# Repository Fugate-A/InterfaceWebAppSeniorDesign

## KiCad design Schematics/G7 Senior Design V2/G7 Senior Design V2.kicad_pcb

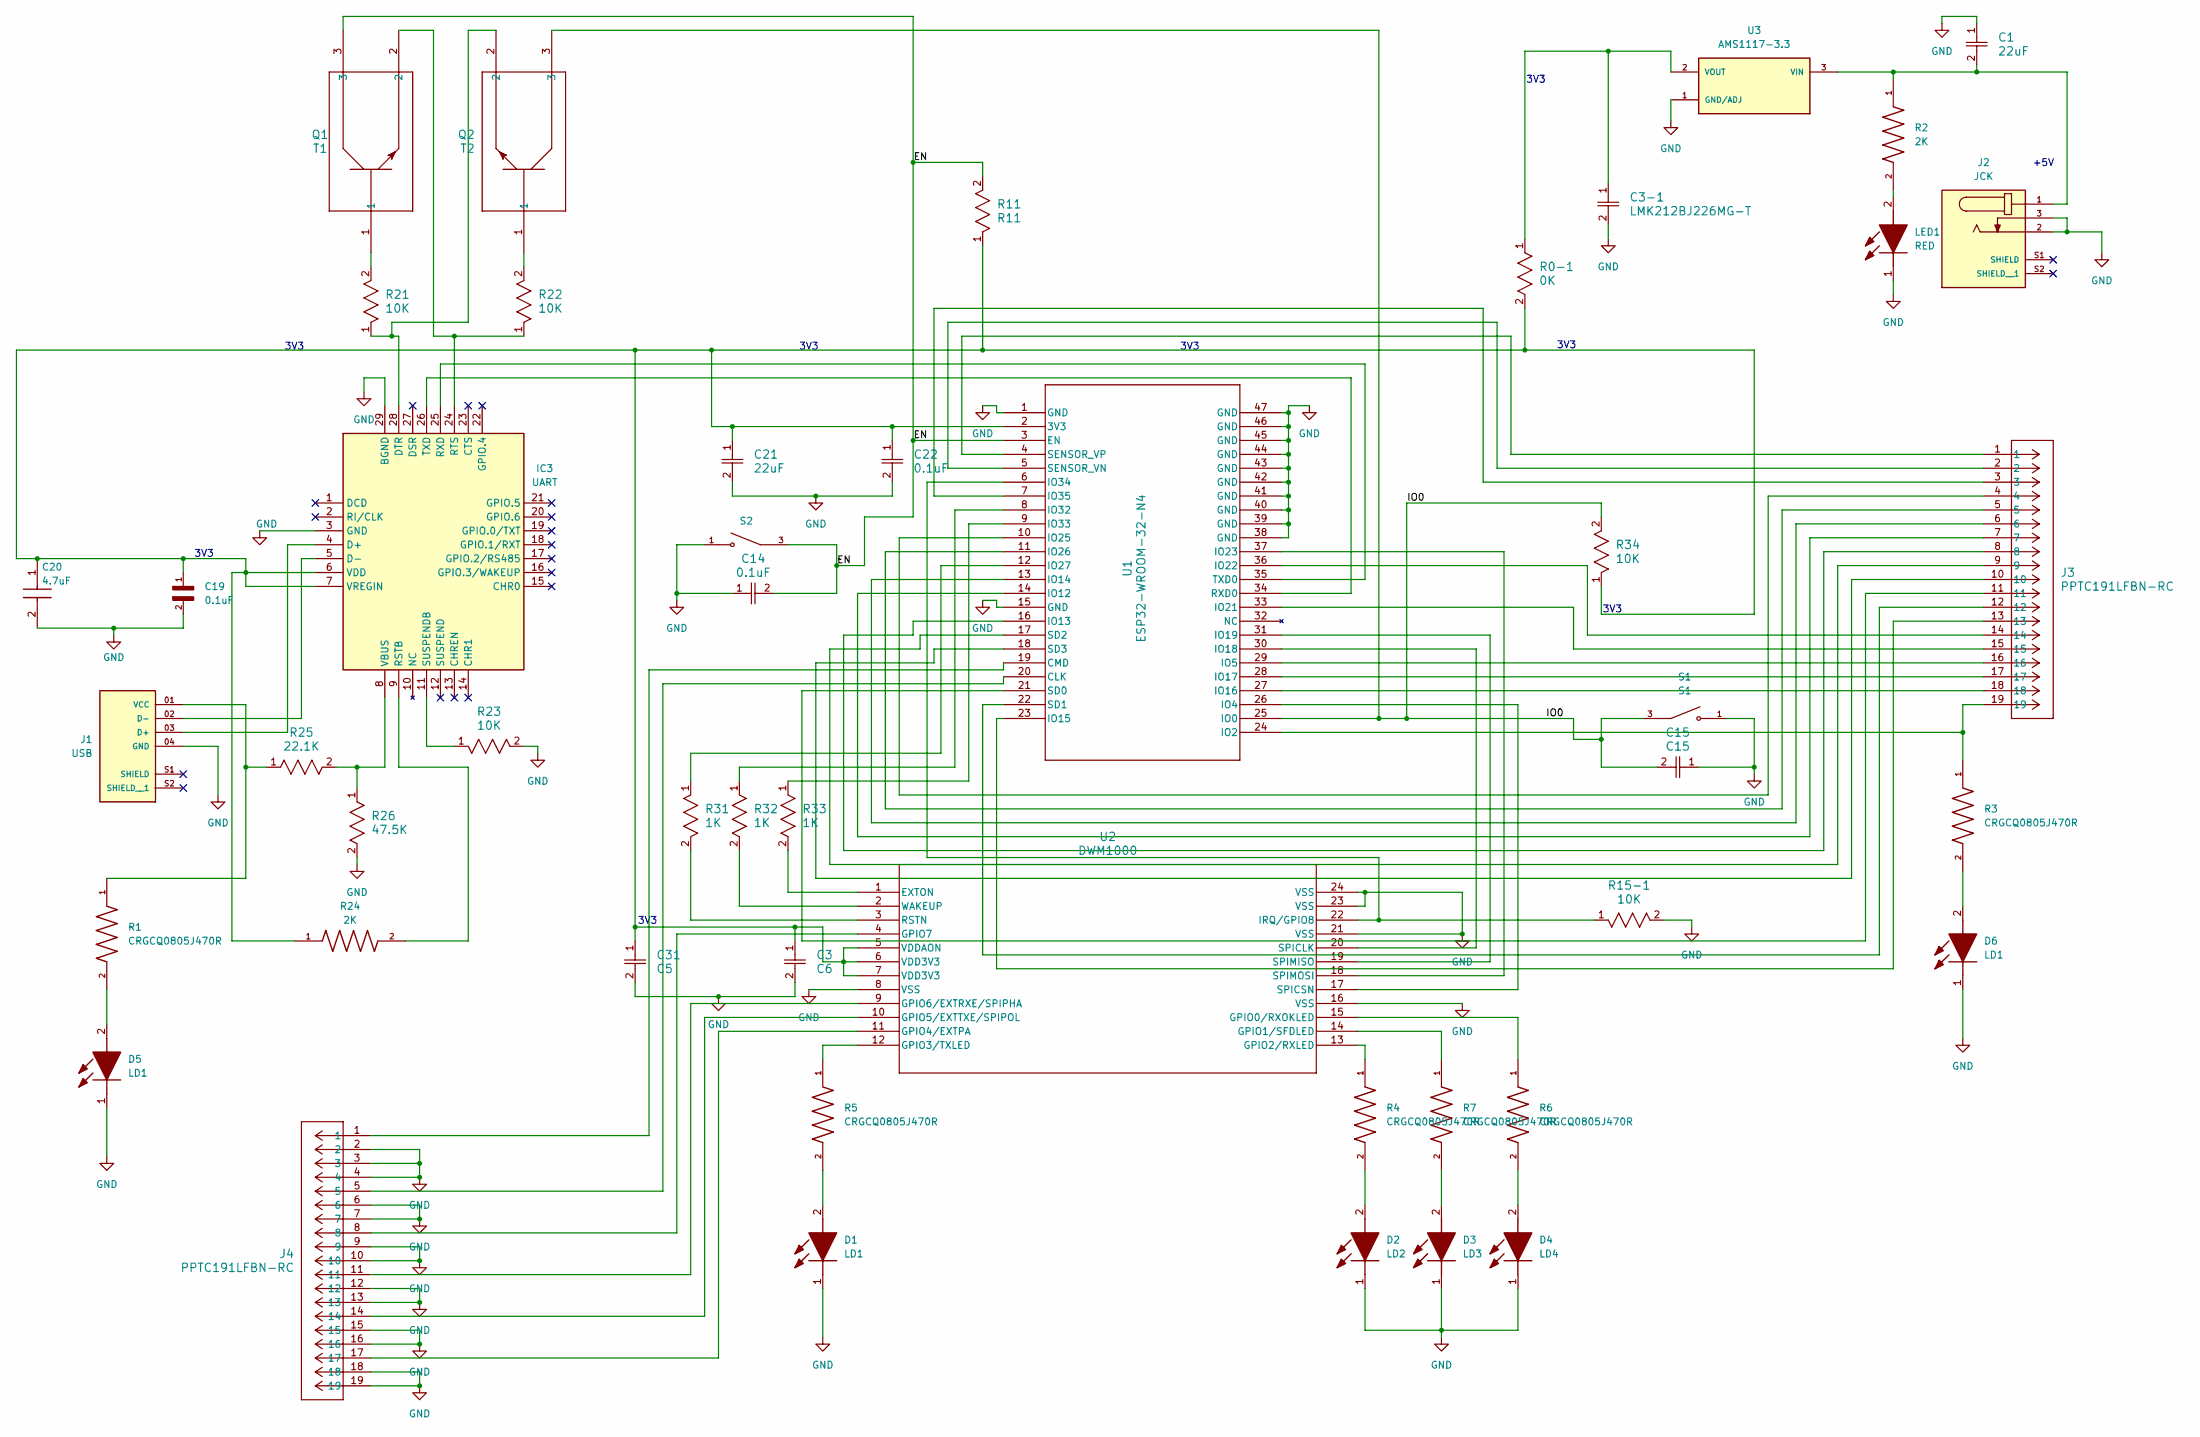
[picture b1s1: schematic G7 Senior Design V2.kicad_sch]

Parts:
C1, C21: 22uF; CAP_LMK212AB7106MG-T_TAY
C3: C6; CC0805N_YAG
C3-1: LMK212BJ226MG-T; CAP_LMK212AB7106MG-T_TAY
C14, C22: 0.1uF; CC0805N_YAG
C15: C15; CC0805N_YAG
C19: 0.1uF; CAPC2012X145N
C20: 4.7uF; CAPC2012X95N; Mouser Part Number 81-GRM219C80J475KE9D
C31: C5; CAP_LMK212AB7106MG-T_TAY
D1, D5, D6: LD1; LEDC2012X90N; Mouser Part Number 630-HSMW-C170-U0000
D2: LD2; LEDC2012X90N; Mouser Part Number 630-HSMW-C170-U0000
D3: LD3; LEDC2012X90N; Mouser Part Number 630-HSMW-C170-U0000
D4: LD4; LEDC2012X90N; Mouser Part Number 630-HSMW-C170-U0000
IC3: UART; QFN50P500X500X80-29N-D; Mouser Part Number 634-CP2102NA02GQFN28
J1: USB; AMPHENOL_87583-2010RLF; PARTREV AD
J2: JCK; CUI_PJ-051AH; PART_REV 1.0
J3, J4: PPTC191LFBN-RC; CONN19_PPTC191LFBN-RC_SUL
LED1: RED; LEDC2012X90N; Mouser Part Number 630-HSMW-C170-U0000
Q1: T1; TRAN_SS8050-G_CIP
Q2: T2; TRAN_SS8050-G_CIP
R0-1: 0K; STA_RMCF0805_STP
R1, R3, R4, R5, R6, R7: CRGCQ0805J470R; RESC2012X65N
R2, R24: 2K; RESC2012X60N
R11: R11; RC0805N_PAN
R15-1, R21, R22, R23, R34: 10K; RC0805N_PAN
R25: 22.1K; STA_RMCF0805_STP
R26: 47.5K; STA_RMCF080547.5K_STP
R31, R32, R33: 1K; RC0805N_YAG
S1: S1; SW_PTS_647_SN50_SMTR2_LFS; PARTREV 4 Apr 22
S2: S2; SW_PTS_647_SN50_SMTR2_LFS; PARTREV 4 Apr 22
U1: ESP32-WROOM-32-N4; MOD_ESP32-WROOM-32_EXP
U2: DWM1000; MOD_DWM1000_QOR
U3: AMS1117-3.3; SOT229P700X180-4N; PARTREV N/A

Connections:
/EN: C14.2, Q1.3, R11.2, S2.3, U1.3 (EN); also elsewhere on the board
/IO0: C15.2, Q2.3, R34.2, S1.3, U1.25 (IO0); also elsewhere on the board
GND: C1.1, C3.2, C3-1.2, C14.1, C15.1, C19.2, C20.2, C21.2, C22.2, C31.2, D1.1 (K), D2.1 (K), D3.1 (K), D4.1 (K), D5.1 (K), D6.1 (K), IC3.3 (GND), IC3.29 (BGND), J1.04 (GND), J2.2, J2.3, J4.2, J4.3, J4.4, J4.6, J4.7, J4.9, J4.10, J4.12, J4.13, J4.15, J4.16, J4.18, J4.19, LED1.1 (K), R15-1.2, R23.2, R26.2, S1.1, S2.1, U1.1 (GND), U1.15 (GND), U1.38 (GND), U1.39 (GND), U1.40 (GND), U1.41 (GND), U1.42 (GND), U1.43 (GND), U1.44 (GND), U1.45 (GND), U1.46 (GND), U1.47 (GND), U2.8 (VSS), U2.16 (VSS), U2.21 (VSS), U2.23 (VSS), U2.24 (VSS), U3.1 (GND/ADJ); also elsewhere on the board
unnamed: D1.2 (A), R5.2
unnamed: D2.2 (A), R4.2
unnamed: D3.2 (A), R7.2
unnamed: D4.2 (A), R6.2
unnamed: D5.2 (A), R1.2
unnamed: D6.2 (A), R3.2
unnamed: IC3.4 (D+), J1.03 (D+)
unnamed: IC3.5 (D-), J1.02 (D-)
unnamed: IC3.28 (DTR), Q2.2, R21.1
unnamed: IC3.9 (RSTB), R24.2
unnamed: IC3.24 (RTS), Q1.2, R22.1
unnamed: IC3.25 (RXD), U1.35 (TXD0)
unnamed: IC3.11 (SUSPENDB), R23.1
unnamed: IC3.26 (TXD), U1.34 (RXD0)
unnamed: IC3.8 (VBUS), R25.2, R26.1
unnamed: C3.1, C19.1, C20.1, C21.1, C22.1, C31.1, IC3.6 (VDD), IC3.7 (VREGIN), R0-1.2, R11.1, R24.1, R34.1, U1.2 (3V3), U2.5 (VDDAON), U2.6 (VDD3V3), U2.7 (VDD3V3)
unnamed: J1.01 (VCC), R1.1, R25.1
unnamed: LED1.2 (A), R2.2
unnamed: Q1.1, R21.2
unnamed: Q2.1, R22.2
unnamed: J4.5, U1.20 (CLK)
unnamed: J4.1, U1.19 (CMD)
unnamed: J3.19, R3.1, U1.24 (IO2)
unnamed: U1.26 (IO4), U2.17 (SPICSN)
unnamed: J3.16, U1.29 (IO5)
unnamed: J3.7, U1.14 (IO12)
unnamed: J3.8, U1.16 (IO13)
unnamed: J3.6, U1.13 (IO14)
unnamed: J3.13, U1.23 (IO15)
unnamed: J3.18, U1.27 (IO16)
unnamed: J3.17, U1.28 (IO17)
unnamed: U1.30 (IO18), U2.20 (SPICLK)
unnamed: U1.31 (IO19), U2.19 (SPIMISO)
unnamed: J3.15, U1.33 (IO21)
unnamed: J3.14, U1.36 (IO22)
unnamed: U1.37 (IO23), U2.18 (SPIMOSI)
unnamed: J3.4, U1.10 (IO25)
unnamed: J3.5, U1.11 (IO26)
unnamed: R31.1, U1.12 (IO27)
unnamed: R32.1, U1.8 (IO32)
unnamed: R33.1, U1.9 (IO33)
unnamed: R15-1.1, U1.6 (IO34), U2.22 (IRQ/GPIO8)
unnamed: J3.3, U1.7 (IO35)
unnamed: J3.11, U1.21 (SD0)
unnamed: J3.12, U1.22 (SD1)
unnamed: J3.9, U1.17 (SD2)
unnamed: J3.10, U1.18 (SD3)
unnamed: J3.2, U1.5 (SENSOR_VN)
unnamed: J3.1, U1.4 (SENSOR_VP)
unnamed: R33.2, U2.1 (EXTON)
unnamed: R6.1, U2.15 (GPIO0/RXOKLED)
unnamed: R7.1, U2.14 (GPIO1/SFDLED)
unnamed: R4.1, U2.13 (GPIO2/RXLED)
unnamed: R5.1, U2.12 (GPIO3/TXLED)
unnamed: J4.17, U2.11 (GPIO4/EXTPA)
unnamed: J4.14, U2.10 (GPIO5/EXTTXE/SPIPOL)
unnamed: J4.11, U2.9 (GPIO6/EXTRXE/SPIPHA)
unnamed: J4.8, U2.4 (GPIO7)
unnamed: R31.2, U2.3 (RSTN)
unnamed: R32.2, U2.2 (WAKEUP)
unnamed: C1.2, J2.1, R2.1, U3.3 (VIN)
unnamed: C3-1.1, R0-1.1, U3.2 (VOUT)

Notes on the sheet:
3V3
+5V

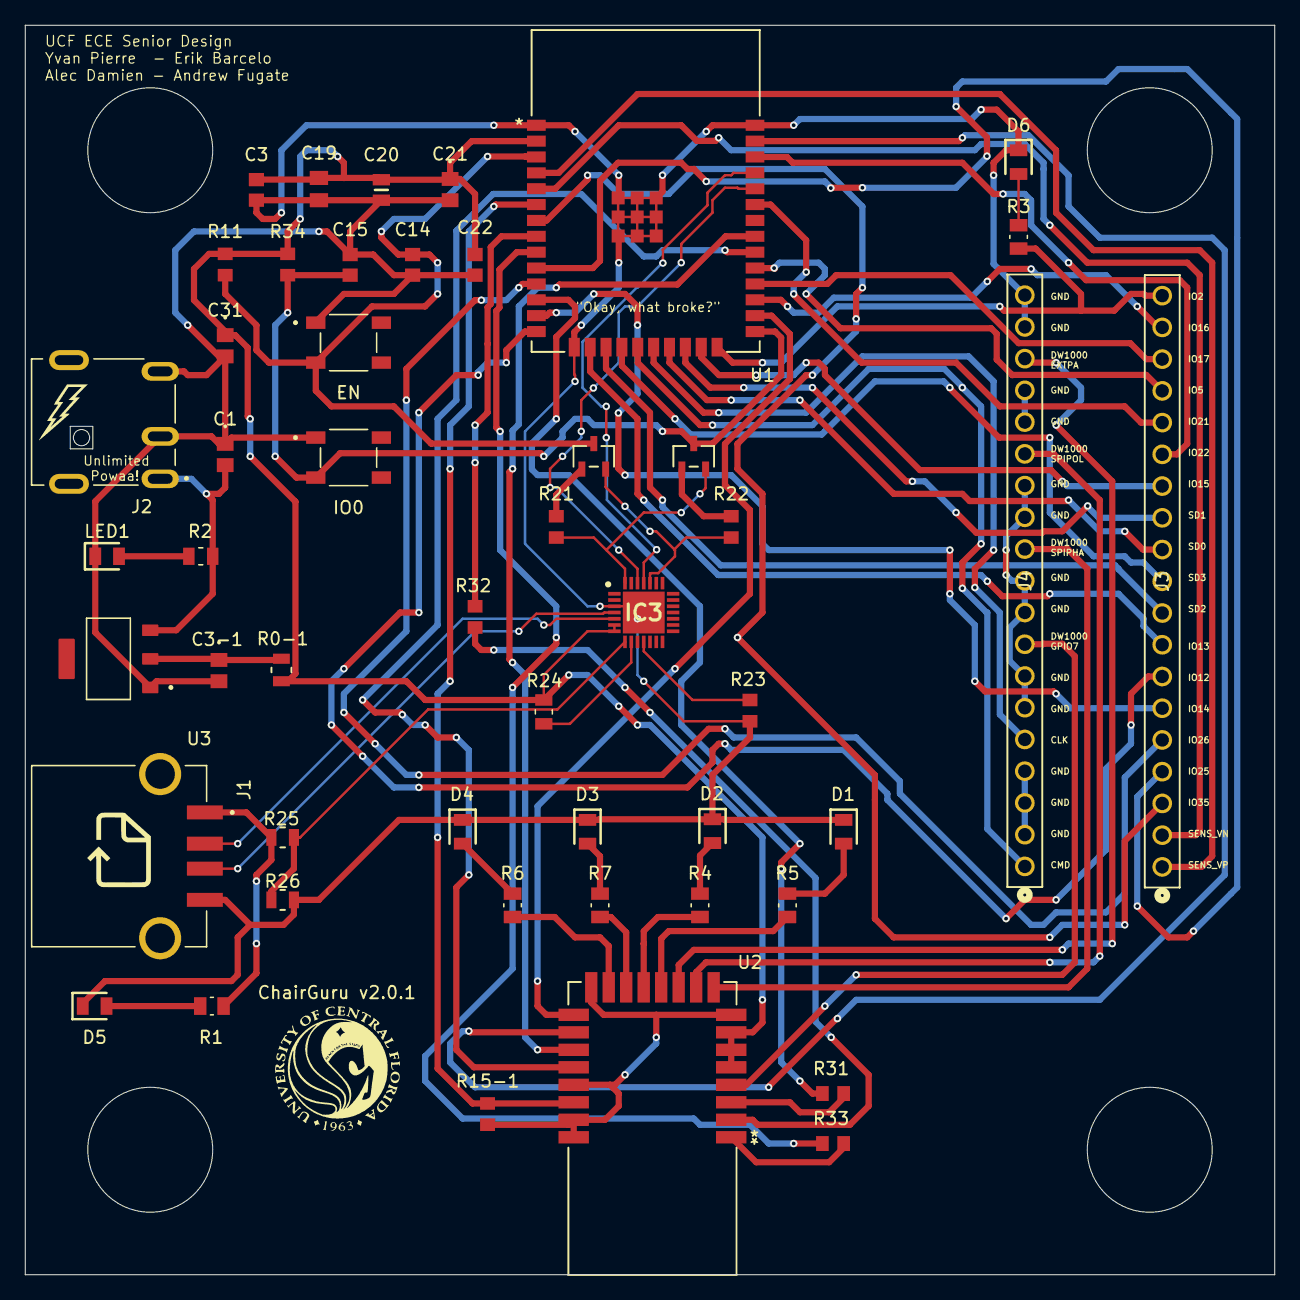
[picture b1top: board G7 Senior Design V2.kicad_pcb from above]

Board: 2 copper layers, 100.0 x 100.0 mm, 49 parts (0 on the bottom side), 65 nets.

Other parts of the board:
EN: S2; SW_PTS_647_SN50_SMTR2_LFS
IO0: S1; SW_PTS_647_SN50_SMTR2_LFS

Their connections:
/EN: EN.3; also elsewhere on the board
/IO0: IO0.3; also elsewhere on the board
GND: EN.1, IO0.1; also elsewhere on the board

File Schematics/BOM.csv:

"Id;""Designator"";""Footprint"";""Quantity"";""Designation"";""Supplier and ref"";",,,,
"1;""J4","J3"";""CONN19_PPTC191LFBN-RC_SUL"";2;""PPTC191LFBN-RC"";;;",,,
"2;""C1","C21"";""CAP_LMK212AB7106MG-T_TAY"";2;""22uF"";;;",,,
"3;""R26"";""STA_RMCF080547.5K_STP"";1;""47.5K"";;;",,,,
"4;""D2"";""LEDC2012X90N"";1;""LD2"";;;",,,,
"5;""S2"";""SW_PTS_647_SN50_SMTR2_LFS"";1;""S2"";;;",,,,
"6;""R11"";""RC0805N_PAN"";1;""R11"";;;",,,,
"7;""R25"";""STA_RMCF0805_STP"";1;""22.1K"";;;",,,,
"8;""D1"";""LEDC2012X90N"";1;""LD1"";;;",,,,
"9;""C14","C22"";""CC0805N_YAG"";2;""0.1uF"";;;",,,
"10;""R6",R5,R4,"R7"";""RESC2012X65N"";4;""CRGCQ0805J470R"";;;",
"11;""J2"";""CUI_PJ-051AH"";1;""JCK"";;;",,,,
"12;""U2"";""MOD_DWM1000_QOR"";1;""DWM1000"";;;",,,,
"13;""C19"";""CAPC2012X95N"";1;""0.1uF"";;;",,,,
"14;""R32"";""RES_1220_SUS"";1;""RD2"";;;",,,,
"15;""C31"";""CAP_LMK212AB7106MG-T_TAY"";1;""C5"";;;",,,,
"16;""J1"";""AMPHENOL_87583-2010RLF"";1;""USB"";;;",,,,
"17;""R2","R24"";""RESC2012X60N"";2;""2K"";;;",,,
"18;""R22",R15-1,R23,R21,"R34"";""RC0805N_PAN"";5;""10K"";;;"
"19;""D3"";""LEDC2012X90N"";1;""LD3"";;;",,,,
"20;""Q1"";""TRAN_SS8050-G_CIP"";1;""T1"";;;",,,,
"21;""C3"";""CC0805N_YAG"";1;""C6"";;;",,,,
"22;""R33"";""RES_1220_SUS"";1;""RD3"";;;",,,,
"23;""C15"";""CC0805N_YAG"";1;""C15"";;;",,,,
"24;""C20"";""CAPC2012X95N"";1;""4.7uF"";;;",,,,
"25;""S1"";""SW_PTS_647_SN50_SMTR2_LFS"";1;""S1"";;;",,,,
"26;""U1"";""MOD_ESP32-WROOM-32_EXP"";1;""ESP32-WROOM-32-N4"";;;",,,,
"27;""D4"";""LEDC2012X90N"";1;""LD4"";;;",,,,
"28;""U3"";""SOT229P700X180-4N"";1;""AMS1117-3.3"";;;",,,,
"29;""LED1"";""LEDC2012X90N"";1;""RED"";;;",,,,
"30;""Q2"";""TRAN_SS8050-G_CIP"";1;""T2"";;;",,,,
"31;""IC3"";""QFN50P500X500X80-29N-D"";1;""UART"";;;",,,,
"32;""R0-1"";""STA_RMCF0805_STP"";1;""0K"";;;",,,,
"33;""C3-22uF1"";""CAP_LMK212AB7106MG-T_TAY"";1;""LMK212BJ226MG-T"";;;",,,,
"34;""R31"";""RES_1220_SUS"";1;""RD1"";;;",,,,

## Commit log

2024-07-10 Init react proj
2024-07-10 Setup Phase
    frontend and backend working with cors setup and interaction tested at a basic level, web app ready to be developed
2024-07-10 most filler react code axed and no errors
2024-07-25 ignoring personal workspace file
2024-07-25 small updates for routing
2024-07-26 routes working, new page, lrud movement added, working on rotation
2024-07-28 ROTATION AND MOVEMENT working !!!
2024-07-28 Colliosion blocking added
2024-07-30 getting ready for more interconnectivity via env and server js
2024-08-19 .env added to ignore
2024-08-22 api for saving works via postman, working for port 5000 but react stuck on 3000, need to add load feature after fixing this
2024-08-22 saving to mongo atlas works!!! now need to load from mongo
2024-08-23 reading id from mongo works now need to rework to display the reads and not just id
2024-08-23 api.js comments cleaned up for da ocd
2024-09-03 updated index, api, and server .js files preparing for merge and collaberators. Fixed mongo names to be real rather than the testing/implementing phase
2024-09-03 FavIcon and tab name updated as well as some of App.js
2024-09-03 create layout page works with adding of custom box layouts, merging before contuning to load
2024-09-04 loading configs to visaulize works but needs adjusting, nothing breaking rn, needs to make new branch cuz i forgor
2024-09-05 Layout list page displays name of layout saved in mongo
2024-09-06 stashing changes - not working
2024-09-06 adding folder for eric to add schematic of PCB
2024-09-06 not working but committing before losing lol
2024-09-06 adding text box
    just to learn Git, we put a text box!!!!!!!!!!!!!!
2024-09-09 Added Changes from Last Meeting
2024-09-09 random kicad stuff
2024-09-09 Weeks Revision before Jungle of Words
2024-09-09 labels adjusted
2024-09-12 First Version to be Ordered from JLCPCB
    Associated schematic with first Gerber file to be sent out to JLCPCB to be fabricated.
2024-09-12 Ensuring Git-Push prior to ordering
2024-09-12 added logos and final review, going to order
2024-09-12 One Page Error Report Gerber
2024-09-12 Initial BOM added
2024-09-13 Updated Gerber and BOM 13 SEP 24
2024-10-01 overview now shoes 1 config, need to update display but works for that
2024-10-03 commit arduino stuff forgetting schematic changes
2024-10-03 testing stuff
    dw1000 communciates but code doesnt work, still a dub
2024-10-06 ChairGuru V1.1
    Updated Changes According to Doc as of 06 OCT 24.
2024-10-07 current in lab model
2024-10-07 ChairGuru 7 OCT 24 NIGHT
    Andrew's Updated Content
2024-10-11 ChairGuru V2.0.1
    11 OCT 24 Updates
2024-10-11 added esp data sheet
2024-10-12 Overview shows chairs now yay
2024-10-12 path planning but no reotation remberance, intial implementation without refinment, generic algo's
2024-10-12 handles x and y movement and then finishes with rotation, good stopping point until antenna integration is needed
2024-10-16 DRV8825 V1
    Custom PCB for Motor Drivers
2024-10-17 css stuff added and env updated to allow for ip access from hotspot
2024-10-17 collision avoidance early imp.. done for night
2024-10-21 init motor code branch
2024-10-21 esp connects to wifi and loops to continue checking status
2024-10-21 updated package json details and working on websocket
    websocket connects but now adding manual testing and then autoamted sending
2024-10-22 not working comms
    esp connects to wifi but does not maintain websocket connection, incoudes esp code and socket.js code
2024-10-23 Added 4 motor code to drive forward
2024-10-23 motor code for 4 motors on v2.0.1 board headers
2024-10-23 space
2024-10-23 working pin out and directory for 4 motor control
2024-10-24 testing library for soft-AP use case
2024-10-24 esp soft-ap working and logging simple http button request from x device to esp32 console
2024-10-24 Websocket is working and full-duplex between a third party device and esp communicate to server pc
2024-10-31 triangle push, may delete later
2024-11-01 Triangulation Code update
    Update, all functional, missing 2nd tag code. Distance calculation afterward
2024-11-01 Test on Chassis
2024-11-04 Updated Motor Code. Everything is accurate except rotation.
2024-11-04 Bug fixes
2024-11-05 not working with motor code but esp hotspot is somwhat working, added api call on overview.js
2024-11-05 wireless netwroking from server now controls motors via access point
2024-11-06 updated motor code and addded buttons to frontend for testing
2024-11-08 Update of Triangulation-Code
    Anchor Code1/2 - Officially ready and done.
    Tag Code 1/2 - http server need some help. but are properly ready to give a location to the server. Need to create TagCode2
    link.cpp has been updated to output x,y coordinates and handle data differently.
2024-11-08 updated some motor code and accidently some recon, switching branches
2024-11-08 chairguru ssid replacing esp access point
2024-11-08 Wi-fi updates
    Wi-fi updates
2024-11-09 motor code push
2024-11-09 reading and storing to database, only anchor 2, not concurrently
2024-11-09 both anchors working and showing data in mongo, integration done network wise
2024-11-09 rough visual pos working, ending branch here
2024-11-10 Updated acceleration and included if statements for low step counts
2024-11-10 somewhat working 2d depth mapping
2024-11-10 anchors working and reporting tag specific location (ie which chasis)
2024-11-10 Fixed if statements, added back translateLeft
2024-11-11 not working combo, mind schredded, come back another time
2024-11-12 combo code working WITH MOTORS ONLY, but no compilation errors
    combo progress with motors, implementing tag and anchors to work together now, ALL PRIOR TO PATH PLANNING
2024-11-12 motors working with cpp files and while including tag stuff, not integrated yet
2024-11-13 merging schematics to clear branches
2024-11-13 forgot stl's
2024-11-14 working tag coordinates with anchors and motor control via post commands - WORKING HERE
2024-11-14 motor commands working, tag info being read, erroring out on 404 server response for storing json tag data
2024-11-14 working motor control with anchors reading pos, editing anchors going forward to save posistions, NOT tag
2024-11-14 FULL COMMUNICATION WORKING 🗣
2024-11-15 small update, not broken
2024-11-15 untested, managing dual tags now on new branch
2024-11-15 Updated Motor Code, functions now accept steps as arguments and do not convert to inches. For reference, 655 steps == 1 meter
2024-11-15 fixed ALECS mistake ( missing ")" added )
2024-11-15 working for visual and for manual control
2024-11-15 Slowed down RPM to hopefully increase torque/eliminate pulling left
2024-11-15 no errors in overview and testing recon
2024-11-15 combo and combo2 addressable by ip, recon gives total path planning but at too large of a scale
2024-11-16 DEMO RECORDED WE GONE GOLD
2024-11-19 untested overview visual updates and some motor code with estop to test
2024-11-19 revert motor code, visuals stuff looking ok
2024-11-19 visuals for landing page, overview, and automove look good, working here for everything functional
2024-11-19 recon looks good and working
2024-11-19 create doesnt look that nice but looks better
2024-11-19 create ok
2024-11-19 layout list is nicer
2024-11-20 dance mode on cos branch
2024-11-25 Final CAD files added to GIT, ready to merge all branches to main and deploy package
2024-11-26 .env files being added manually
    .env files used for global and hidden var info within the webapp. Local keys only; removed online keys present before it worked completely offline
2024-11-26 FinalPushWithDemoOfApp
2024-11-26 WebAppDemoPics
    GitHub can't embed videos so here are pics
2024-11-26 DiagramsAddedFromOneDrive
